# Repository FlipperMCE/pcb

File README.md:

# FlipperMCE - PCB and Case

This repository contains the pcb files and the case for FlipperMCE - a GameCube Memory Card Emulator.

## PCB

Production files (gerbers/bom/cpl) for JLCPCB can be found in the releases section.

When ordering the PCB, make sure to use the following settings:

- 0.8 mm thickness
- ENIG finish

For the "connector" version, a display needs to be ordered separately.
Make sure, the display has a 0.5mm pitch with 30 Pins.
These displays can be found at aliexpress or other market places.

## Case

The case files are located in the ```case``` folder. For normal use, you would print:

- FlipperMCE_Bottom_v1.stl
- FlipperMCE_top_v1.stl
- FlipperMCE_Buttons_v1.stl
- either FlipperMCE_DisplayBracket_v1.stl or FlipperMCE_DisplayBracket_alter_v1.stl

Make sure to follow the assembly guide at [https://flippermce.github.io](https://flippermce.github.io) .

## Special Thanks

Special thanks goes to BitFunX (@gameBitfunx) for providing the pcb and case files for FlipperMCE <3!

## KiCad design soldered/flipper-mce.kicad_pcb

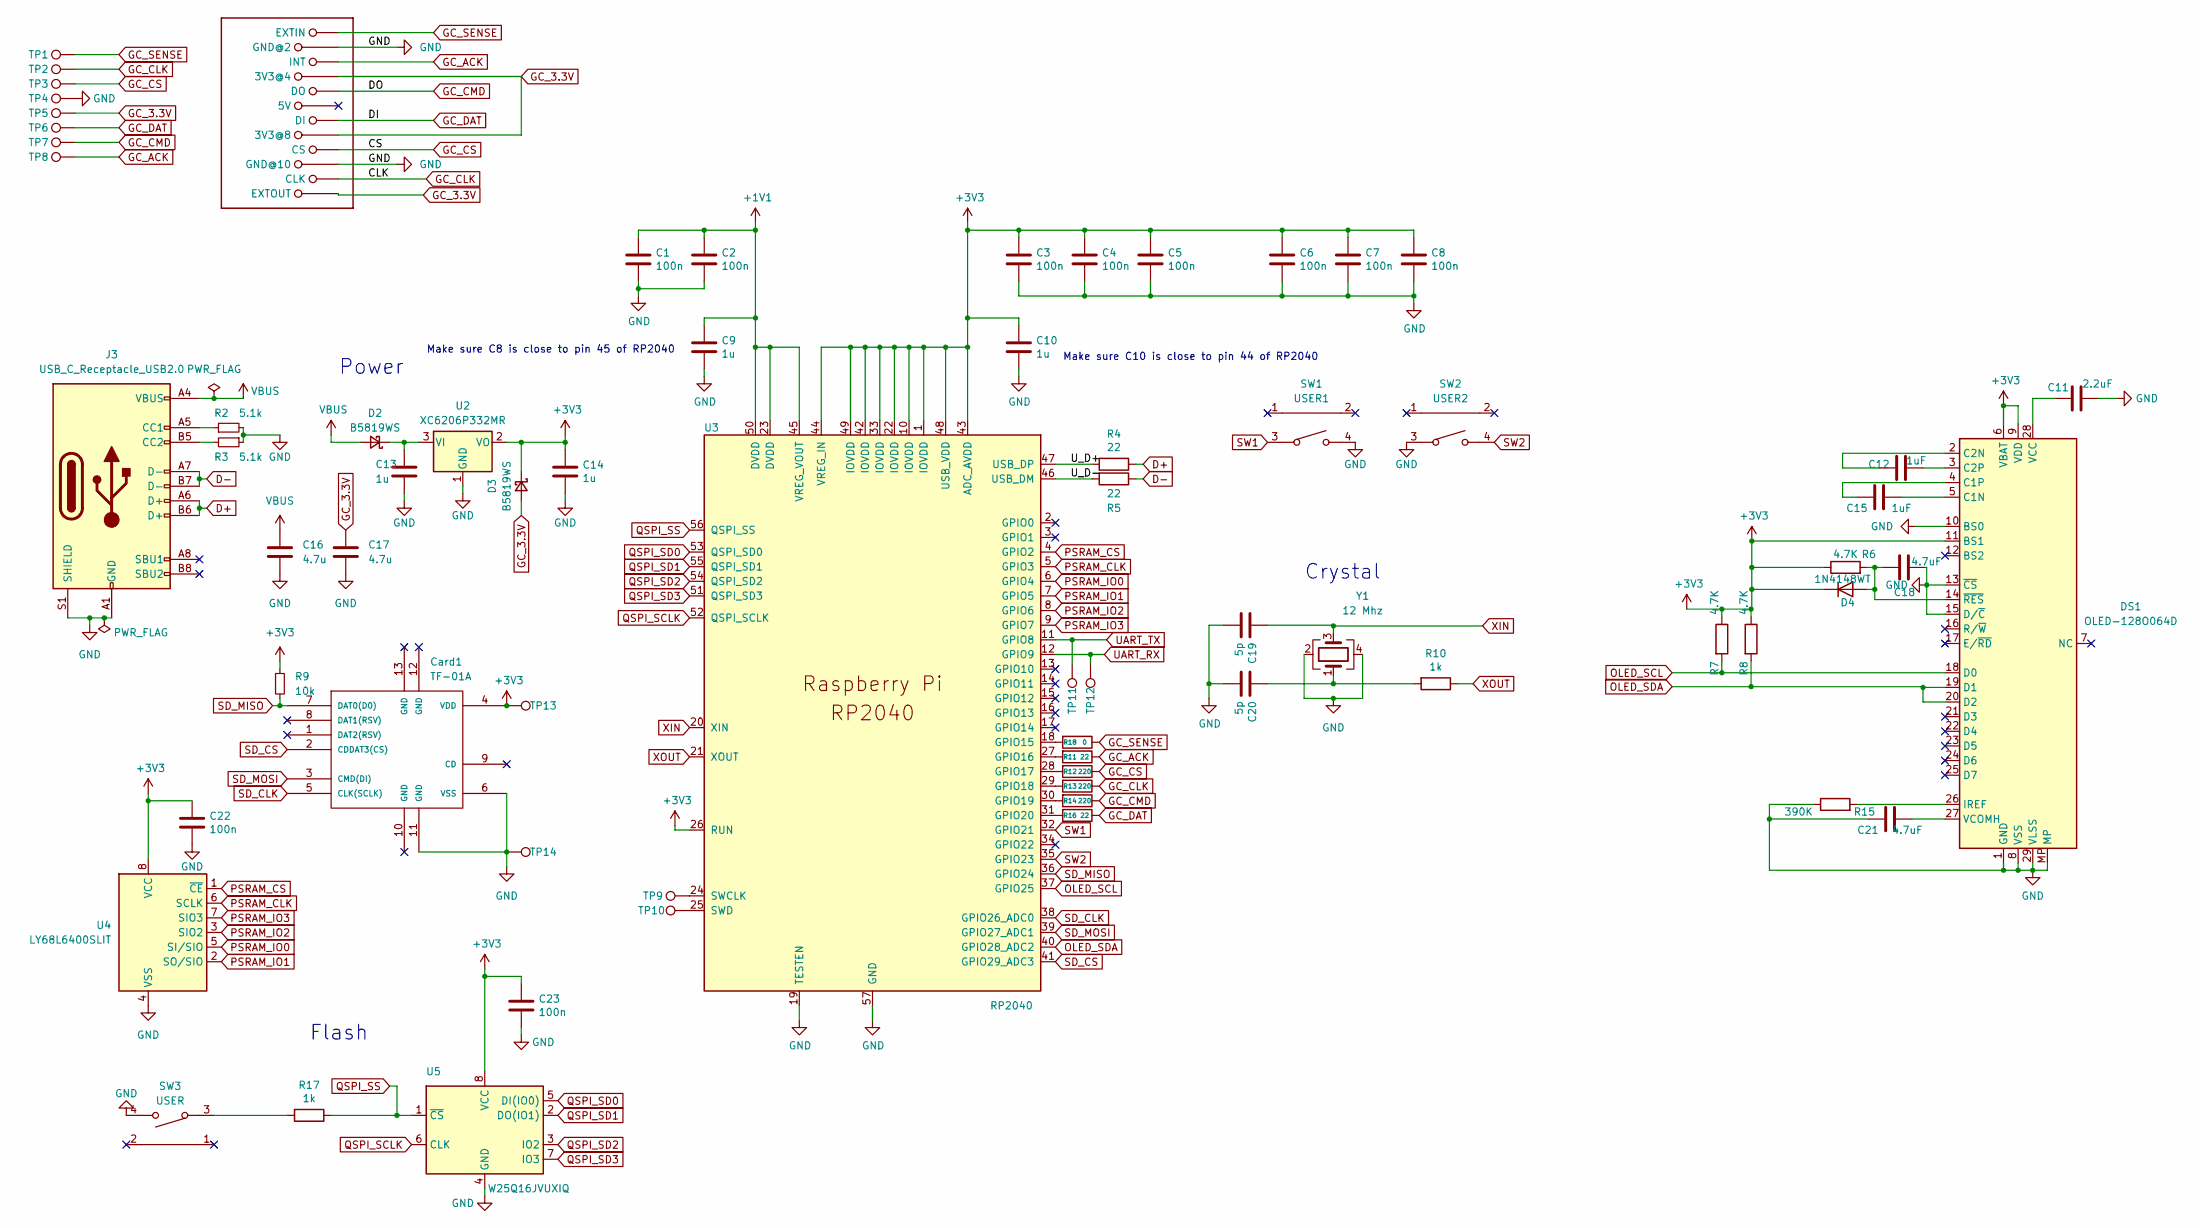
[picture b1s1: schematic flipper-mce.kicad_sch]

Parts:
C1, C2, C3, C4, C5, C6, C7, C8, C22, C23: 100n; C_0402_1005Metric; LCSC C1525
C9, C10, C13, C14: 1u; C_0402_1005Metric; LCSC C52923
C11: 2.2uF; C_0603_1608Metric
C12, C15: 1uF; C_0402_1005Metric
C16, C17: 4.7u; C_0603_1608Metric; LCSC C23733
C18, C21: 4.7uF; C_0603_1608Metric
C19, C20: 5p; C_0402_1005Metric; LCSC C1570
Card1: TF-01A; TF-SMD_TF-01A; LCSC C91145
D2, D3: B5819WS; D_SOD-323; LCSC C191023
D4: 1N4148WT; D_SOD-523
DS1: OLED-128O064D; GC_OLED_096
J2: GC_MEMCARD
J3: USB_C_Receptacle_USB2.0; USB_C_Receptacle_HRO_TYPE-C-31-M-12; LCSC C2765186
R2, R3: 5.1k; R_0402_1005Metric; LCSC C25905
R4, R5, R11, R16: 22; R_0402_1005Metric; LCSC C25092
R6, R7, R8: 4.7K; R_0402_1005Metric
R9: 10k; R_0402_1005Metric; LCSC C25744
R10, R17: 1k; R_0402_1005Metric; LCSC C11702
R12, R13, R14: 220; R_0402_1005Metric; LCSC C25091
R15: 390K; R_0402_1005Metric
R18: 0; R_0402_1005Metric; LCSC C25092
SW1: USER1; SW-SMD_TS24CA; LCSC C393942
SW2: USER2; SW-SMD_TS24CA; LCSC C393942
SW3: USER; SW-SMD_TS24CA; LCSC C393942
TP1, TP2, TP3, TP4, TP5, TP6, TP7, TP8, TP9, TP10, TP11, TP12, TP13, TP14: TestPoint; TestPoint_Pad_D1.0mm
U2: XC6206P332MR; SOT-23; LCSC C5446
U3: RP2040; RP2040-QFN-56; LCSC C2040
U4: LY68L6400SLIT; SOIC-8_3.9x4.9mm_P1.27mm; LCSC C261881
U5: W25Q16JVUXIQ; USON-8_2x3mm_P0.5mm; LCSC C97521
Y1: 12 Mhz; Crystal_SMD_3225-4Pin_3.2x2.5mm; LCSC C9002

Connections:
+1V1: C1.1, C2.1, C9.1, U3.23 (DVDD), U3.45 (VREG_VOUT), U3.50 (DVDD)
+3V3: C3.1, C4.1, C5.1, C6.1, C7.1, C8.1, C10.1, C14.1, C22.1, C23.1, Card1.4 (VDD), D3.1 (K), D4.1 (K), DS1.6 (VBAT), DS1.9 (VDD), DS1.11 (BS1), R6.1, R7.1, R8.1, R9.1, TP13.1, U2.2 (VO), U3.1 (IOVDD), U3.10 (IOVDD), U3.22 (IOVDD), U3.26 (RUN), U3.33 (IOVDD), U3.42 (IOVDD), U3.43 (ADC_AVDD), U3.44 (VREG_IN), U3.48 (USB_VDD), U3.49 (IOVDD), U4.8 (VCC), U5.8 (VCC)
/U_D+: R4.2, U3.47 (USB_DP)
/U_D-: R5.2, U3.46 (USB_DM)
D+: J3.A6 (D+), J3.B6 (D+), R4.1
D-: J3.A7 (D-), J3.B7 (D-), R5.1
GC_3.3V: C17.2, D3.2 (A), J2.4 (3V3@4), J2.8 (3V3@8), J2.12 (EXTOUT), TP5.1
GC_ACK: J2.3 (INT), R11.1, TP8.1
GC_CLK: J2.11 (CLK), R13.1, TP2.1
GC_CMD: J2.5 (DO), R14.1, TP7.1
GC_CS: J2.9 (CS), R12.1, TP3.1
GC_DAT: J2.7 (DI), R16.1, TP6.1
GC_SENSE: J2.1 (EXTIN), R18.1, TP1.1
GND: C1.2, C2.2, C3.2, C4.2, C5.2, C6.2, C7.2, C8.2, C9.2, C10.2, C11.2, C13.2, C14.2, C16.1, C17.1, C18.2, C19.2, C20.2, C21.1, C22.2, C23.2, Card1.6 (VSS), Card1.11 (GND), DS1.1 (GND), DS1.8 (VSS), DS1.10 (BS0), DS1.13 (~CS), DS1.15 (D/~C), DS1.29 (VLSS), DS1.30 (GND), DS1.MP, J2.2 (GND@2), J2.10 (GND@10), J3.A1 (GND), J3.A12 (GND), J3.B1 (GND), J3.B12 (GND), J3.S1 (SHIELD), R2.2, R3.1, R15.1, SW1.4, SW2.3, SW3.4, TP4.1, TP14.1, U2.1 (GND), U3.19 (TESTEN), U3.57 (GND), U4.4 (VSS), U5.4 (GND), Y1.2, Y1.4
unnamed: C20.1, R10.2, Y1.1
unnamed: C13.1, D2.1 (K), U2.3 (VI)
unnamed: C18.1, D4.2 (A), DS1.14 (~RES), R6.2
unnamed: C15.2, DS1.5 (C1N)
unnamed: C15.1, DS1.4 (C1P)
unnamed: C12.1, DS1.2 (C2N)
unnamed: C12.2, DS1.3 (C2P)
unnamed: DS1.26 (IREF), R15.2
unnamed: C11.1, DS1.28 (VCC)
unnamed: C21.2, DS1.27 (VCOMH)
unnamed: J3.A5 (CC1), R2.1
unnamed: J3.B5 (CC2), R3.2
unnamed: R17.2, SW3.3
unnamed: R18.2, U3.18 (GPIO15)
unnamed: R11.2, U3.27 (GPIO16)
unnamed: R12.2, U3.28 (GPIO17)
unnamed: R13.2, U3.29 (GPIO18)
unnamed: R14.2, U3.30 (GPIO19)
unnamed: R16.2, U3.31 (GPIO20)
unnamed: TP9.1, U3.24 (SWCLK)
unnamed: TP10.1, U3.25 (SWD)
OLED_SCL: DS1.18 (D0), R7.2, U3.37 (GPIO25)
OLED_SDA: DS1.19 (D1), DS1.20 (D2), R8.2, U3.40 (GPIO28_ADC2)
PSRAM_CLK: U3.5 (GPIO3), U4.6 (SCLK)
PSRAM_CS: U3.4 (GPIO2), U4.1 (~CE)
PSRAM_IO0: U3.6 (GPIO4), U4.5 (SI/SIO)
PSRAM_IO1: U3.7 (GPIO5), U4.2 (SO/SIO)
PSRAM_IO2: U3.8 (GPIO6), U4.3 (SIO2)
PSRAM_IO3: U3.9 (GPIO7), U4.7 (SIO3)
QSPI_SCLK: U3.52 (QSPI_SCLK), U5.6 (CLK)
QSPI_SD0: U3.53 (QSPI_SD0), U5.5 (DI(IO0))
QSPI_SD1: U3.55 (QSPI_SD1), U5.2 (DO(IO1))
QSPI_SD2: U3.54 (QSPI_SD2), U5.3 (IO2)
QSPI_SD3: U3.51 (QSPI_SD3), U5.7 (IO3)
QSPI_SS: R17.1, U3.56 (QSPI_SS), U5.1 (~CS)
SD_CLK: Card1.5 (CLK(SCLK)), U3.38 (GPIO26_ADC0)
SD_CS: Card1.2 (CDDAT3(CS)), U3.41 (GPIO29_ADC3)
SD_MISO: Card1.7 (DAT0(D0)), R9.2, U3.36 (GPIO24)
SD_MOSI: Card1.3 (CMD(DI)), U3.39 (GPIO27_ADC1)
SW1: SW1.3, U3.32 (GPIO21)
SW2: SW2.4, U3.35 (GPIO23)
UART_RX: TP12.1, U3.12 (GPIO9)
UART_TX: TP11.1, U3.11 (GPIO8)
VBUS: C16.2, D2.2 (A), J3.A4 (VBUS), J3.A9 (VBUS), J3.B4 (VBUS), J3.B9 (VBUS)
XIN: C19.1, U3.20 (XIN), Y1.3
XOUT: R10.1, U3.21 (XOUT)

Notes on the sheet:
Make sure C8 is close to pin 45 of RP2040
Flash
Crystal
Power
Make sure C10 is close to pin 44 of RP2040

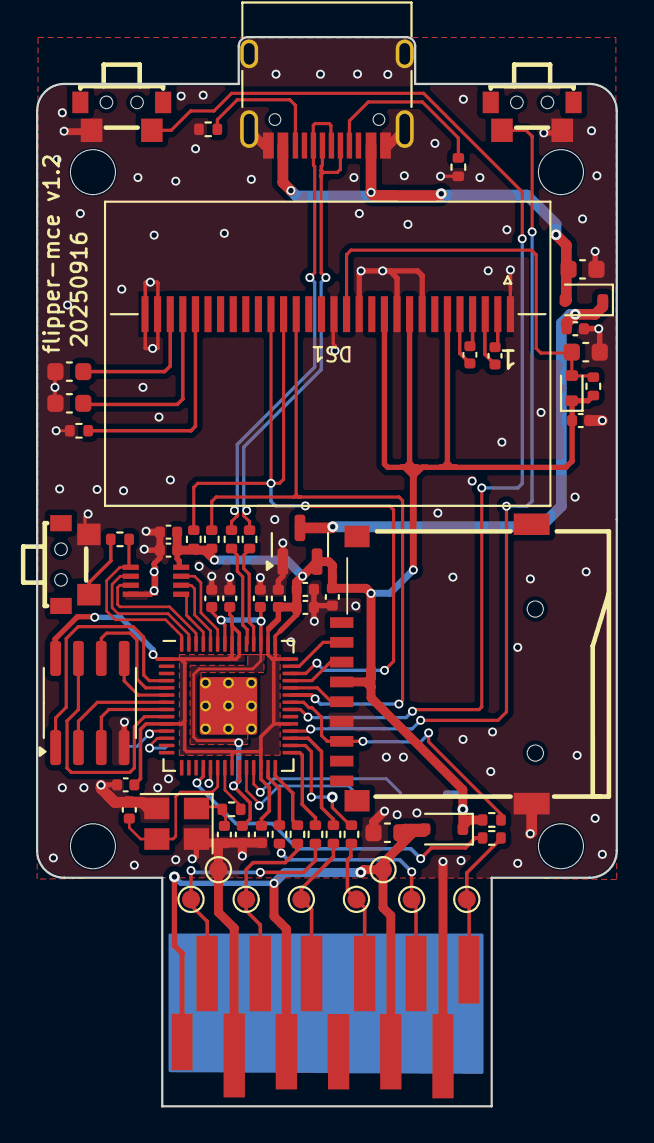
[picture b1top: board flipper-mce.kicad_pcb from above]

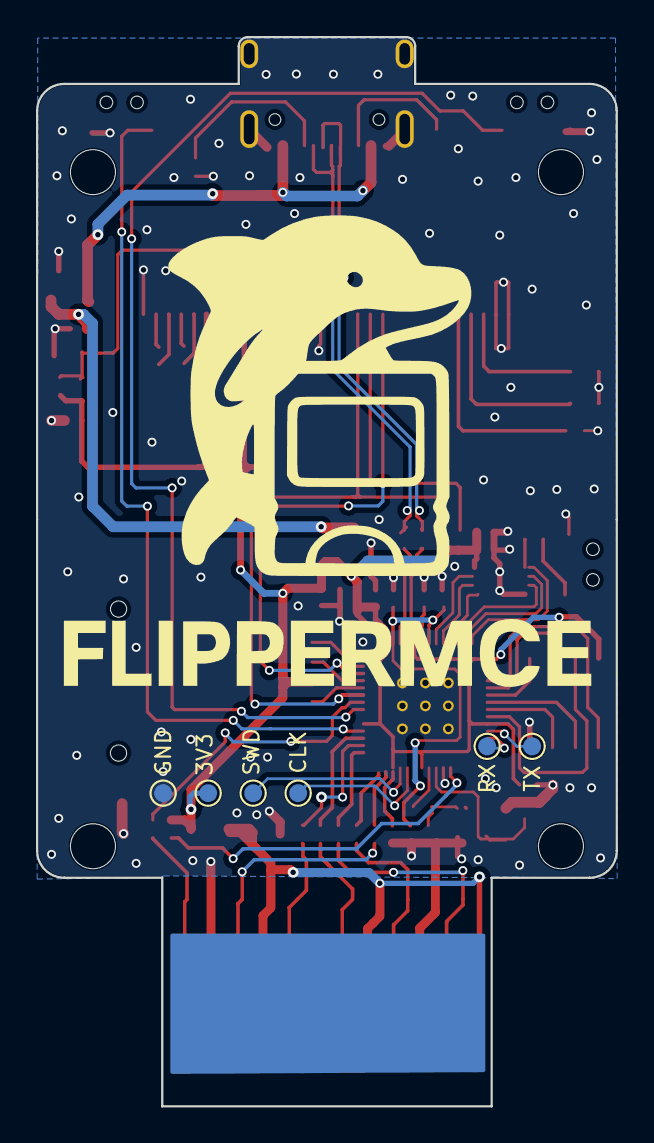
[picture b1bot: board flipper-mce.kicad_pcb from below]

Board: 2 copper layers, 32.2 x 59.4 mm, 69 parts (7 on the bottom side), 60 nets.

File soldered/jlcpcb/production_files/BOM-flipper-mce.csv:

Comment,Designator,Footprint,LCSC,Quantity
1k,"R10,R17",R_0402_1005Metric,C11702,2
100n,"C1,C2,C22,C23,C3,C4,C5,C6,C7,C8",C_0402_1005Metric,C1525,10
5p,"C19,C20",C_0402_1005Metric,C1570,2
B5819WS,"D2,D3",D_SOD-323,C191023,2
RP2040,U3,RP2040-QFN-56,C2040,1
2.2uF,C11,C_0603_1608Metric,C23630,1
4.7u,"C16,C17,C18,C21",C_0603_1608Metric,C23733,4
220,"R12,R13,R14",R_0402_1005Metric,C25091,3
22,"R11,R16,R18,R4,R5",R_0402_1005Metric,C25092,5
10k,R9,R_0402_1005Metric,C25744,1
390K,R15,R_0402_1005Metric,C25782,1
4.7K,"R6,R7,R8",R_0402_1005Metric,C25900,3
5.1k,"R2,R3",R_0402_1005Metric,C25905,2
LY68L6400SLIT,U4,SOIC-8_3.9x4.9mm_P1.27mm,C261881,1
USB_C_Receptacle_USB2.0,J3,USB_C_Receptacle_HRO_TYPE-C-31-M-12,C2765186,1
1N4148WT,D4,D_SOD-523,C27748,1
W25Q16JVUXIQ,U5,USON-8_2x3mm_P0.5mm,C2843335,1
OLED-128O064D,DS1,GC_OLED_096,C2890596,1
USER1,"SW1,SW2,SW3",SW-SMD_TS24CA,C393942,3
1u,"C10,C12,C13,C14,C15,C9",C_0402_1005Metric,C52923,6
XC6206P332MR,U2,SOT-23,C5446,1
12 Mhz,Y1,Crystal_SMD_3225-4Pin_3.2x2.5mm,C9002,1
TF-01A,Card1,TF-SMD_TF-01A,C91145,1
TestPoint,TP5,TestPoint_Pad_D1.0mm,,1
~,J2,GC_MEMCARD,,1
TestPoint,TP4,TestPoint_Pad_D1.0mm,,1
TestPoint,TP7,TestPoint_Pad_D1.0mm,,1
TestPoint,TP8,TestPoint_Pad_D1.0mm,,1
TestPoint,TP1,TestPoint_Pad_D1.0mm,,1
TestPoint,TP2,TestPoint_Pad_D1.0mm,,1
TestPoint,TP6,TestPoint_Pad_D1.0mm,,1
TestPoint,TP3,TestPoint_Pad_D1.0mm,,1
TestPoint,TP10,TestPoint_Pad_D1.0mm,,1
TestPoint,TP9,TestPoint_Pad_D1.0mm,,1
TestPoint,TP14,TestPoint_Pad_D1.0mm,,1
TestPoint,TP13,TestPoint_Pad_D1.0mm,,1
TestPoint,TP12,TestPoint_Pad_D1.0mm,,1
TestPoint,TP11,TestPoint_Pad_D1.0mm,,1

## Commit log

2025-09-12 Initial commit Case
2025-09-13 Fix Cap values
2025-09-13 Create LICENSE
2025-09-14 Alternative display bracket
2025-09-14 Add Case model stp
2025-09-16 Altered Layout for soldered OLED
2025-09-17 Fix BOM and CPL
2025-09-17 Remove production files for soldered
2025-09-24 Fix Connector
